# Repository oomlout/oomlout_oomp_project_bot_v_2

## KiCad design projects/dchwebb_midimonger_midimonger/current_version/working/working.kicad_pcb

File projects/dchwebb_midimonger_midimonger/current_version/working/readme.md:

# midimonger
 
## summary 
* id: dchwebb_midimonger_midimonger
* user: dchwebb
* name: midimonger
* board: midimonger
* repo: https://github.com/dchwebb/MidiMonger
* src_file_repo_kicad_pcb: Hardware/MidiMonger.kicad_pcb
* src_file_repo_kicad_pcb_link: https://github.com/dchwebb/MidiMonger/tree/master/Hardware/MidiMonger.kicad_pcb
* src_file_repo_kicad_sch: Hardware/MidiMonger.kicad_sch
* src_file_repo_kicad_sch_link: https://github.com/dchwebb/MidiMonger/tree/master/Hardware/MidiMonger.kicad_sch

* src_file_repo_sch: Hardware/MidiMonger.sch
* src_file_repo_sch_link: https://github.com/dchwebb/MidiMonger/tree/master/Hardware/MidiMonger.sch
* full details link: https://github.com/oomlout/oomlout_oomp_project_bot_v_2/tree/main/projects/dchwebb_midimonger_midimonger/current_version/working

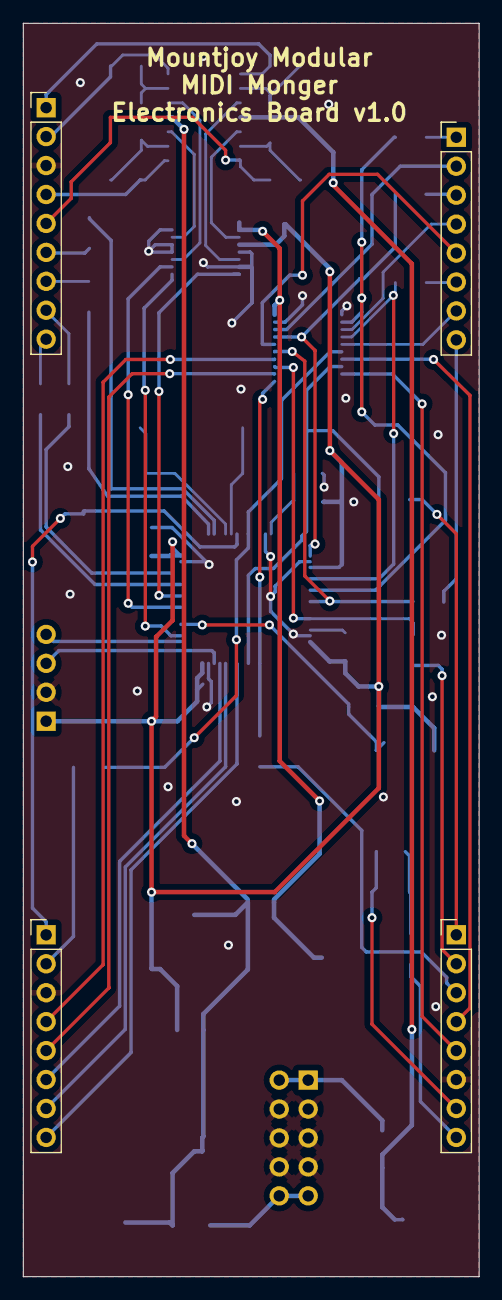
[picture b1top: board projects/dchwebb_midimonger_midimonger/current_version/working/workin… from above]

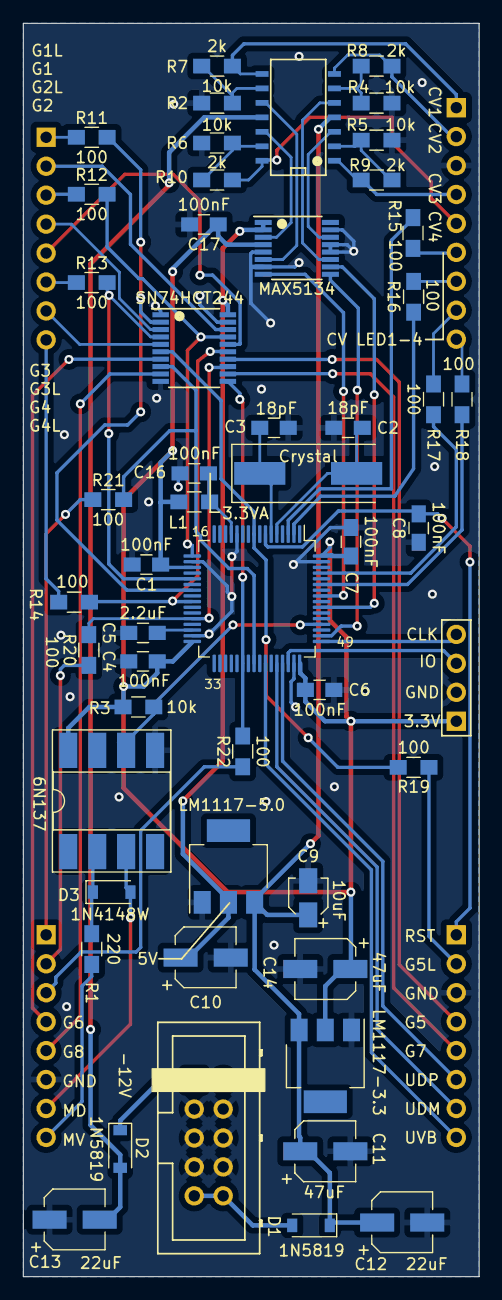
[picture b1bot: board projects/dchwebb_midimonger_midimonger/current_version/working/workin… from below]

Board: 2 copper layers, 40.0 x 110.0 mm, 56 parts (52 on the bottom side), 68 nets.

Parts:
C1, C4, C6, C7, C8, C16, C17: 100nF; C_0805_HandSoldering
C2, C3: 18pF; C_0805_HandSoldering
C5: 2.2uF; C_0805_HandSoldering
C9: 10uF; CP_Elec_3x5.3
C10, C12, C13: 22uF; CP_Elec_5x5.3
C11, C14: 47uF; CP_Elec_5x5.8
D1, D2: 1N5819; D_SOD-123
D3: 1N4148W; D_SOD-123
J1: SWD_Header; SWD_header
J2: Conn_01x09_Male; Socket_Strip_Straight_1x09_Pitch2.54mm
J3, J4, J5: Conn_01x08_Male; Socket_Strip_Straight_1x08_Pitch2.54mm
J9: Eurorack_10_pin_power; Eurorack_10_pin_header
L1: L; L_0805_HandSoldering
R1: 220; R_0805_HandSoldering
R2, R3, R4, R5, R6: 10k; R_0805_HandSoldering
R7, R8, R9, R10: 2k; R_0805_HandSoldering
R11, R12, R13, R14, R15, R16, R17, R18, R19, R20, R21, R22: 100; R_0805_HandSoldering
U1: STM32F446RETx; LQFP-64_10x10mm_P0.5mm
U2: 6N137; DIP-8_W8.89mm_SMDSocket_LongPads
U3: TL074; SOIC-14_N
U4: LM1117-5.0; SOT-223
U5: LM1117-3.3; SOT-223
U6: SN74HCT244; TSSOP-20_4.4x6.5mm_Pitch0.65mm
U7: MAX5134; TSSOP-16_4.4x5mm_Pitch0.65mm
Y1: Crystal; Crystal_SMD

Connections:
+3.3VA: C16.1, L1.1, U1.13
+3V3: C1.1, C4.1, C6.1, C7.1, C14.1, C17.1, J1.1, L1.2, R3.1, U1.19, U1.32, U1.48, U1.64, U2.8, U5.2, U7.4
+5V: C10.1, U4.2, U6.20, U7.1, U7.2
+12V: D1.2, J9.9, J9.10
-12V: D2.1, J9.1, J9.2
CV1_LED: R15.2, U1.3
CV1_LED_OUT: J2.6, R15.1
CV1_OUT: J2.1, R7.1, U3.8
CV2_LED: R16.2, U1.2
CV2_LED_OUT: J2.7, R16.1
CV2_OUT: J2.2, R8.1, U3.7
CV3_LED: R17.2, U1.61
CV3_LED_OUT: J2.8, R17.1
CV3_OUT: J2.4, R9.1, U3.1
CV4_LED: R18.2, U1.59
CV4_LED_OUT: J2.9, R18.1
CV4_OUT: J2.5, R10.1, U3.14
DAC_1: U3.10, U7.6
DAC_2: U3.5, U7.11
DAC_3: U3.3, U7.14
DAC_4: U3.12, U7.3
DAC_MOSI: U1.57, U7.8
DAC_NSS: U1.50, U7.9
DAC_SCK: U1.55, U7.10
GATE1: R11.2, U1.23, U6.2
GATE1_LED_OUT: J3.1, R11.1
GATE1_OUT: J3.2, U6.18
GATE2: R12.2, U1.17, U6.17
GATE2_LED_OUT: J3.3, R12.1
GATE2_OUT: J3.4, U6.3
GATE3: R13.2, U1.21, U6.4
GATE3_LED_OUT: J3.6, R13.1
GATE3_OUT: J3.5, U6.16
GATE4: R14.2, U1.25, U6.15
GATE4_LED_OUT: J3.8, R14.1
GATE4_OUT: J3.7, U6.5
GATE5: R19.2, U1.9, U6.6
GATE5_LED_OUT: J4.2, R19.1
GATE5_OUT: J4.4, U6.14
GATE6: R20.2, U1.28, U6.13
GATE6_LED_OUT: J5.2, R20.1
GATE6_OUT: J5.4, U6.7
GATE7: R21.2, U1.40, U6.8
GATE7_LED_OUT: J5.1, R21.1
GATE7_OUT: J4.5, U6.12
GATE8: R22.2, U1.38, U6.11
GATE8_LED_OUT: J5.3, R22.1
GATE8_OUT: J5.5, U6.9
GND: C1.2, C2.2, C3.2, C4.2, C5.2, C6.2, C7.2, C8.1, C9.2, C10.2, C11.2, C12.2, C13.1, C14.2, C16.2, C17.2, J1.2, J2.3, J4.3, J5.6, J9.3, J9.4, J9.5, J9.6, J9.7, J9.8, R2.1, R4.1, R5.1, R6.1, U1.12, U1.18, U1.31, U1.47, U1.63, U2.5, U4.1, U5.1, U6.1, U6.10, U6.19, U7.5, U7.7, U7.12, U7.13, U7.15
MIDI_DATA: D3.2, J5.7, U2.3
MIDI_RX: R3.2, U1.52, U2.6
MIDI_VREF: J5.8, R1.2
NRST: C8.2, J4.1, U1.7
unnamed: C2.1, U1.5, Y1.2
unnamed: C3.1, U1.6, Y1.1
unnamed: C5.1, U1.30
unnamed: D3.1, R1.1, U2.2
unnamed: R2.2, R7.2, U3.9
unnamed: R4.2, R8.2, U3.6
unnamed: R5.2, R9.2, U3.2
unnamed: R6.2, R10.2, U3.13
SWCLK: J1.4, U1.49
SWDIO: J1.3, U1.46
USB_DM: J4.7, U1.44
USB_DP: J4.6, U1.45
USB_VBUS: J4.8, U1.42
VCC: C9.1, C11.1, C12.1, D1.1, U3.4, U4.3, U5.3
VEE: C13.2, D2.2, U3.11

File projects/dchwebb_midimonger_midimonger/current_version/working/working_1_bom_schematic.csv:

"Source:","C:\gh\oomlout_oomp_project_bot_v_2\projects\dchwebb_midimonger_midimonger\current_version\working\working_1.kicad_sch"
"Date:","30/09/2023 04:30:42"
"Tool:","Eeschema 7.0.6"
"Generator:","C:/Program Files/KiCad/7.0/bin/scripting/plugins/bom_csv_grouped_by_value_with_fp.py"
"Component Count:","56"
"Ref","Qnty","Value","Cmp name","Footprint","Description","Vendor","DNP"
"C1, C4, C6, C7, C8, C16, C17","7","100nF","C","Capacitors_SMD:C_0805_HandSoldering","Unpolarized capacitor","",""
"C2, C3","2","18pF","C","Capacitors_SMD:C_0805_HandSoldering","Unpolarized capacitor","",""
"C5","1","2.2uF","C","Capacitors_SMD:C_0805_HandSoldering","Unpolarized capacitor","",""
"C9","1","10uF","C","Capacitors_SMD:CP_Elec_3x5.3","Unpolarized capacitor","",""
"C10, C12, C13","3","22uF","CP-Device","Capacitors_SMD:CP_Elec_5x5.3","","",""
"C11, C14","2","47uF","C","Capacitors_SMD:CP_Elec_5x5.8","Unpolarized capacitor","",""
"D1, D2","2","1N5819","1N5819","Diodes_SMD:D_SOD-123","40V 1A Schottky Barrier Rectifier Diode, DO-41","",""
"D3","1","1N4148W","1N4148W","Diodes_SMD:D_SOD-123","75V 0.15A Fast Switching Diode, SOD-123","",""
"J1","1","SWD_Header","Conn_01x04_Male","Custom_Footprints:SWD_header","Generic connector, single row, 01x04, script generated (kicad-library-utils/schlib/autogen/connector/)","",""
"J2","1","Conn_01x09_Male","Conn_01x09_Male","Socket_Strips:Socket_Strip_Straight_1x09_Pitch2.54mm","Generic connector, single row, 01x09, script generated (kicad-library-utils/schlib/autogen/connector/)","",""
"J3, J4, J5","3","Conn_01x08_Male","Conn_01x08_Male","Socket_Strips:Socket_Strip_Straight_1x08_Pitch2.54mm","Generic connector, single row, 01x08, script generated (kicad-library-utils/schlib/autogen/connector/)","",""
"J9","1","Eurorack_10_pin_power","Eurorack_10_pin_power","Custom_Footprints:Eurorack_10_pin_header","","",""
"L1","1","L","L","Inductors_SMD:L_0805_HandSoldering","Inductor","",""
"R1","1","220","R","Resistors_SMD:R_0805_HandSoldering","Resistor","",""
"R2, R3, R4, R5, R6","5","10k","R","Resistors_SMD:R_0805_HandSoldering","Resistor","",""
"R7, R8, R9, R10","4","2k","R","Resistors_SMD:R_0805_HandSoldering","Resistor","",""
"R11, R12, R13, R14, R15, R16, R17, R18, R19, R20, R21, R22","12","100","R","Resistors_SMD:R_0805_HandSoldering","Resistor","",""
"U1","1","STM32F446RETx","STM32F446RETx","Package_QFP:LQFP-64_10x10mm_P0.5mm","ARM Cortex-M4 MCU, 512KB flash, 128KB RAM, 180MHz, 1.8-3.6V, 50 GPIO, LQFP-64","",""
"U2","1","6N137","6N137","Housings_DIP:DIP-8_W8.89mm_SMDSocket_LongPads","High Speed Optocoupler, TTL Compatible, CTR 18%, DIP8","",""
"U3","1","TL074","TL074","SMD_Packages:SOIC-14_N","Quad Low-Noise JFET-Input Operational Amplifiers, DIP-14/SOIC-14","",""
"U4","1","LM1117-5.0","LM1117-5.0","TO_SOT_Packages_SMD:SOT-223","800mA Low-Dropout Linear Regulator, 5.0V fixed output, TO-220/TO-252/TO-263/SOT-223","",""
"U5","1","LM1117-3.3","LM1117-3.3","TO_SOT_Packages_SMD:SOT-223","800mA Low-Dropout Linear Regulator, 3.3V fixed output, TO-220/TO-252/TO-263/SOT-223","",""
"U6","1","SN74HCT244","SN74HCT244","Housings_SSOP:TSSOP-20_4.4x6.5mm_Pitch0.65mm","Octal-Channel Buffer & Line Driver, 3-State, 20-Pin TSSOP","",""
"U7","1","MAX5134","MAX5134","Housings_SSOP:TSSOP-16_4.4x5mm_Pitch0.65mm","Maxim MAX5134AGUE+, 4-Channel Serial DAC, 16-Pin TSSOP","",""
"Y1","1","Crystal","Crystal","Custom_Footprints:Crystal_SMD","Two pin crystal","",""

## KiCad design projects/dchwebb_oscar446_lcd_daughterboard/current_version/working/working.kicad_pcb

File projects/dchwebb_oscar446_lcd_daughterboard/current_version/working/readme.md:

# oscar446
 
## summary 
* id: dchwebb_oscar446_lcd_daughterboard
* user: dchwebb
* name: oscar446
* board: lcd_daughterboard
* repo: https://github.com/dchwebb/Oscar446
* src_file_repo_kicad_pcb: Hardware/lcd_Daughterboard.kicad_pcb
* src_file_repo_kicad_pcb_link: https://github.com/dchwebb/Oscar446/tree/master/Hardware/lcd_Daughterboard.kicad_pcb

* src_file_repo_sch: Hardware/lcd_Daughterboard.sch
* src_file_repo_sch_link: https://github.com/dchwebb/Oscar446/tree/master/Hardware/lcd_Daughterboard.sch
* full details link: https://github.com/oomlout/oomlout_oomp_project_bot_v_2/tree/main/projects/dchwebb_oscar446_lcd_daughterboard/current_version/working

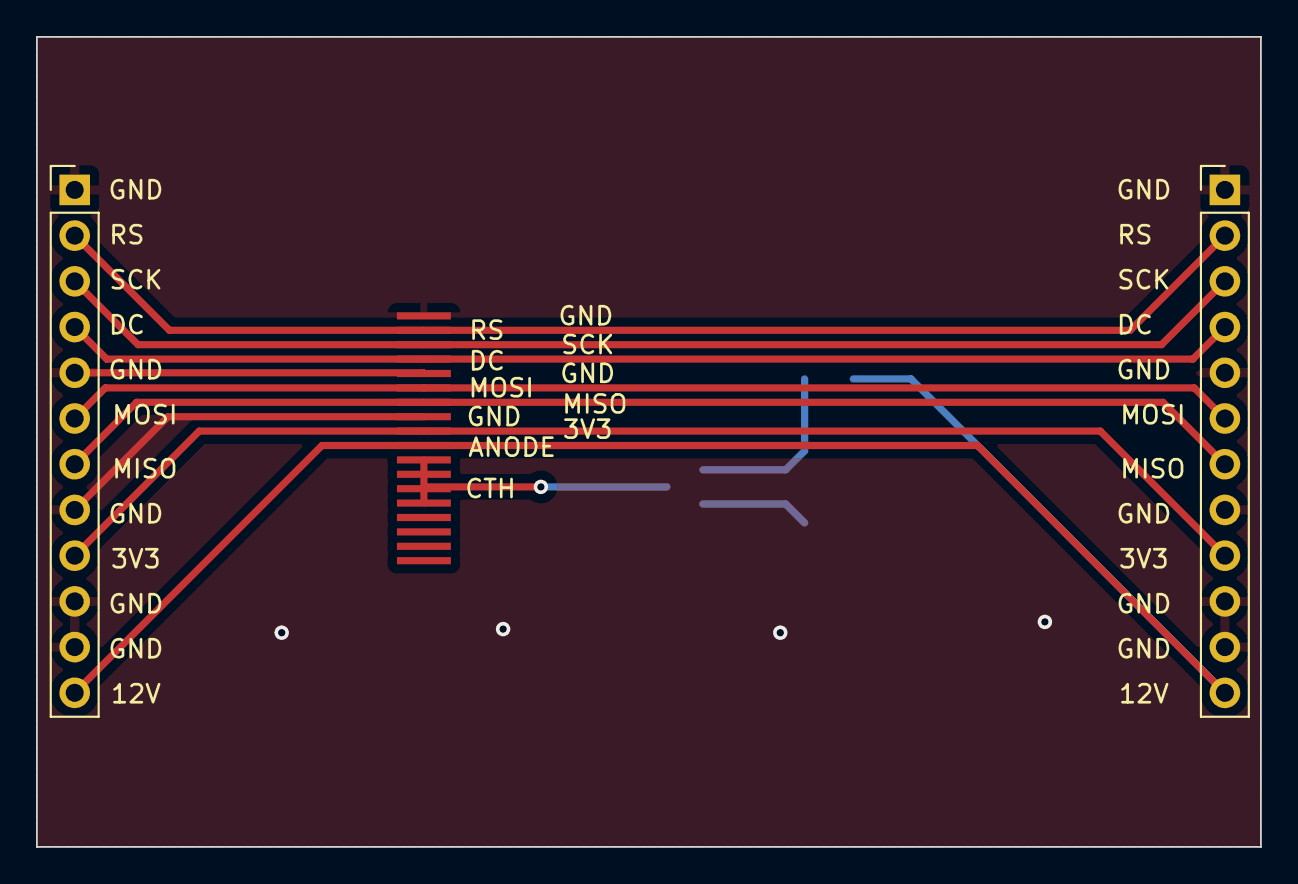
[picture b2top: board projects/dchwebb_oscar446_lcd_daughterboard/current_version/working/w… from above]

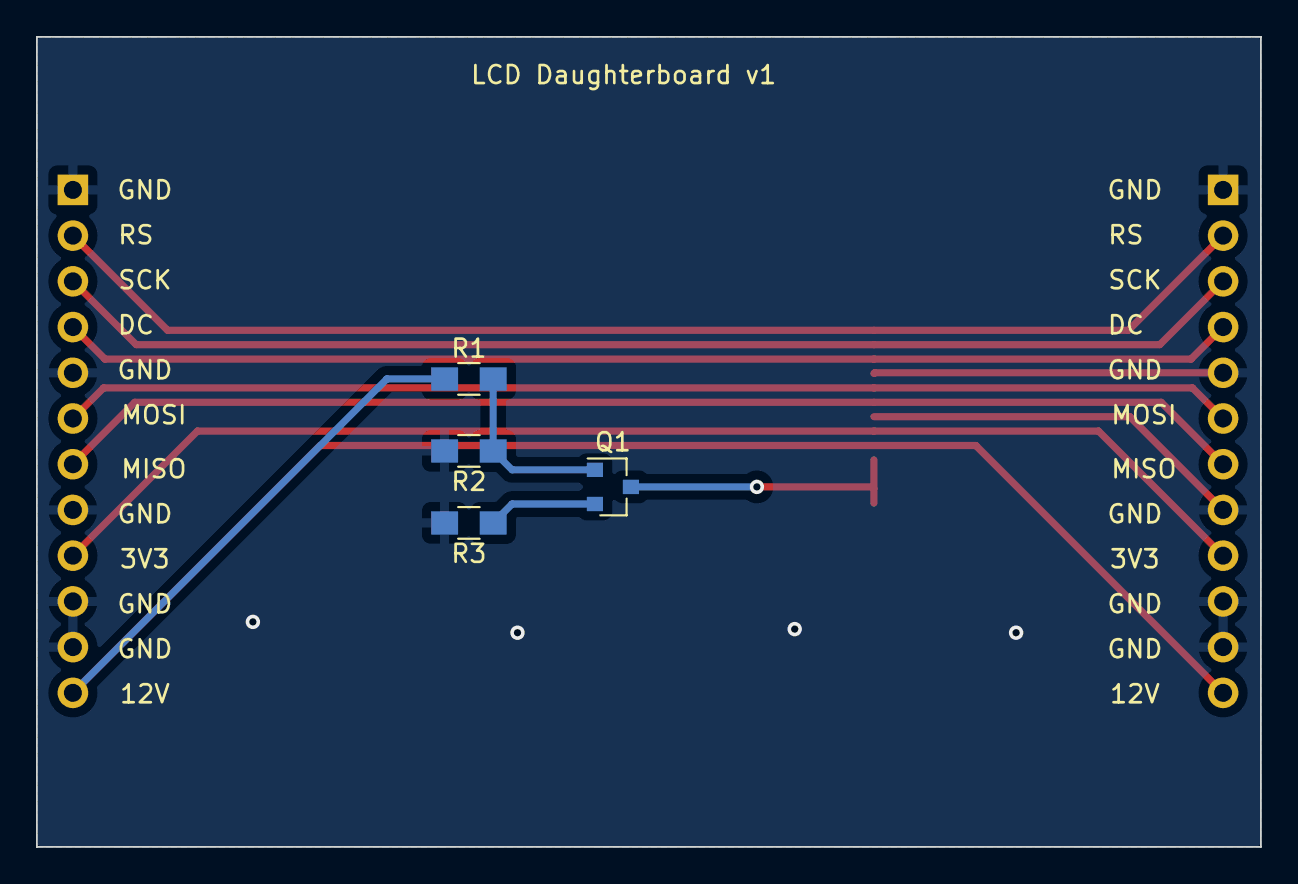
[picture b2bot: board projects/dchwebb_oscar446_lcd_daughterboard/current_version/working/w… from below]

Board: 2 copper layers, 68.0 x 45.0 mm, 7 parts (4 on the bottom side), 11 nets.

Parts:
J1, J2: Conn_01x12; Pin_Header_Straight_1x12_Pitch2.54mm
Q1: MMBT3904; SOT-23
R1: 220; R_0805_HandSoldering
R2: 1k; R_0805_HandSoldering
R3: 100; R_0805_HandSoldering
U1: ILI9341_SPI_Bare; 18x0.8mmLCDConnector

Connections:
+3V3: J1.9, J2.9, U1.9
GND: J1.1, J1.5, J1.8, J1.10, J1.11, J2.1, J2.5, J2.8, J2.10, J2.11, R2.2, R3.2, U1.1, U1.5, U1.8
LCD_CATHODE: Q1.3, U1.11, U1.12, U1.13, U1.14
LCD_DC: J1.4, J2.4, U1.4
LCD_MISO: J1.7, J2.7, U1.7
LCD_MOSI: J1.6, J2.6, U1.6
LCD_RESET: J1.2, J2.2, U1.2
LCD_SCK: J1.3, J2.3, U1.3
unnamed: Q1.1, R1.2, R2.1
unnamed: Q1.2, R3.1
VCC: J1.12, J2.12, R1.1, U1.10

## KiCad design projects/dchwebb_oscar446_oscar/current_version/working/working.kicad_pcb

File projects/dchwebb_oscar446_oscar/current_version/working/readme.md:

# oscar446
 
## summary 
* id: dchwebb_oscar446_oscar
* user: dchwebb
* name: oscar446
* board: oscar
* repo: https://github.com/dchwebb/Oscar446
* src_file_repo_kicad_pcb: Hardware/v1_bu/oscar.kicad_pcb
* src_file_repo_kicad_pcb_link: https://github.com/dchwebb/Oscar446/tree/master/Hardware/v1_bu/oscar.kicad_pcb

* src_file_repo_sch: Hardware/v1_bu/oscar.sch
* src_file_repo_sch_link: https://github.com/dchwebb/Oscar446/tree/master/Hardware/v1_bu/oscar.sch
* full details link: https://github.com/oomlout/oomlout_oomp_project_bot_v_2/tree/main/projects/dchwebb_oscar446_oscar/current_version/working

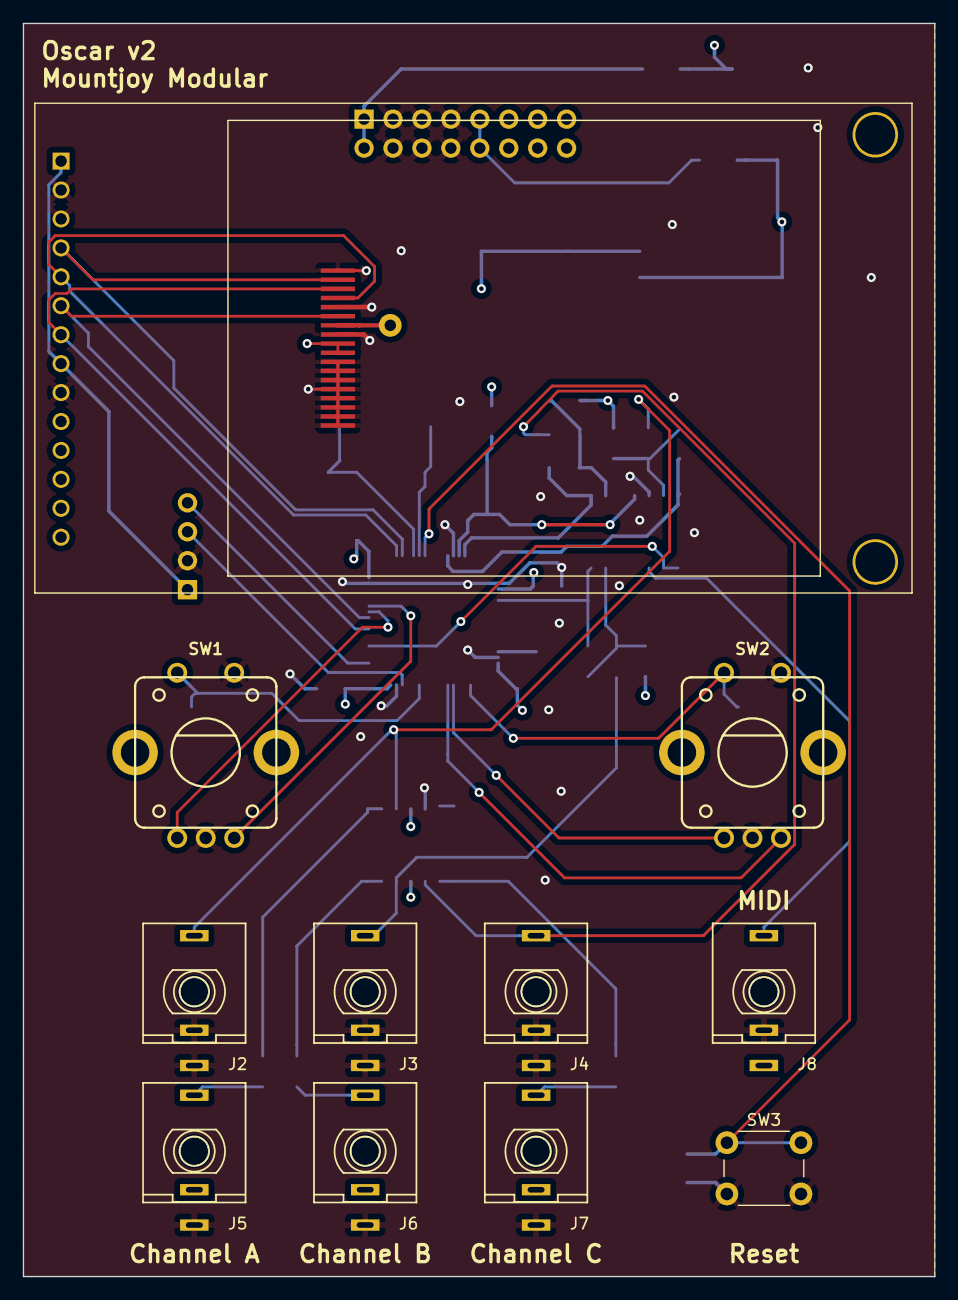
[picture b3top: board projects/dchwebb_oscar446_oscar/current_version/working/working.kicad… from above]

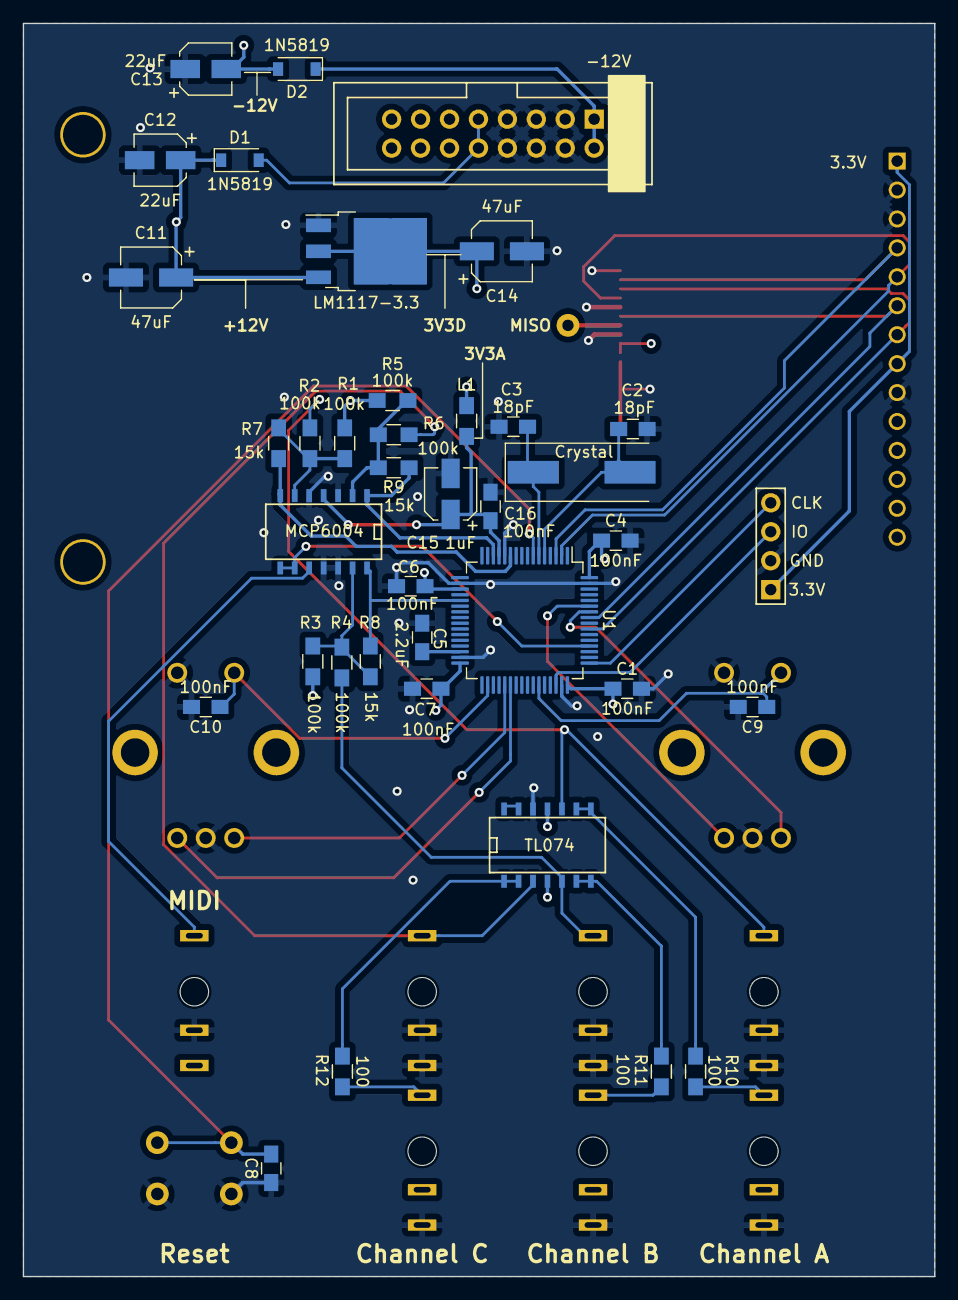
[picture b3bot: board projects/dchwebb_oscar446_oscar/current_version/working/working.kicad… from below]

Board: 4 copper layers, 80.0 x 110.0 mm, 51 parts (38 on the bottom side), 42 nets.

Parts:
C1, C4, C6, C7, C8, C9, C10, C16: 100nF; C_0805_HandSoldering
C2, C3: 18pF; C_0805_HandSoldering
C5: 2.2uF; C_0805_HandSoldering
C11, C14: 47uF; CP_Elec_5x5.8
C12, C13: 22uF; CP_Elec_4x5.8
C15: 1uF; CP_Elec_4x5.8
D1, D2: 1N5819; D_SOD-123
J1: SWD_Header; SWD_header
J2: ChannelA_In; THONKICONN_hole
J3: ChannelB_In; THONKICONN_hole
J4: ChannelC_In; THONKICONN_hole
J5: ChA_Buff_Out; THONKICONN_hole
J6: ChB_Buff_Out; THONKICONN_hole
J7: ChC_Buff_Out; THONKICONN_hole
J8: MIDI_In; THONKICONN_hole
J9: Eurorack_16_pin_power; Eurorack_16_pin_header
J10: LCD_Connector; 18x0.8mmLCDConnector
J11: MISO_Connector; SolderWirePad_single_2mmDrill
L1: L; R_0805_HandSoldering
R1, R2, R3, R4, R5, R6: 100k; R_0805_HandSoldering
R7, R8, R9: 15k; R_0805_HandSoldering
R10, R11, R12: 100; R_0805_HandSoldering
SW1: Left_Encoder; Encoder
SW2: Right_Encoder; Encoder
SW3: SW_Push; SW_PUSH_6mm
U1: STM32F446RETx; LQFP-64_10x10mm_P0.5mm
U2: ILI9341_SPI
U3: MCP6004; SOIC-14_N
U4: TL074; SOIC-14_N
U5: LM1117-3.3; TO-252-3_TabPin2
Y1: Crystal; Crystal_SMD

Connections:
+3.3VA: C15.1, C16.1, L1.1, U1.13, U3.4
+3V3: C1.1, C4.1, C6.1, C7.1, C14.1, J1.1, J10.9, J10.10, L1.2, U1.19, U1.32, U1.48, U1.64, U2.1, U2.8, U5.2
+12V: D1.2, J9.9, J9.10
-12V: D2.1, J9.1, J9.2
/CHA_In: J2.3, R2.2, U4.10
/CHA_Out: J5.3, R10.1
/CHB_In: J3.3, R4.2, U4.5
/CHB_Out: J6.3, R11.1
/CHC_In: J4.3, R6.2, U4.3
/CHC_Out: J7.3, R12.1
/MIDI_In: J8.3, U3.10
CH_A_IN: R7.1, U1.11, U3.7
CH_B_IN: R8.1, U1.21, U3.14
CH_C_IN: R9.1, U1.14, U3.1
GND: C1.2, C2.2, C3.2, C4.2, C5.2, C6.2, C7.2, C8.1, C9.2, C10.2, C11.2, C12.2, C13.1, C14.2, C15.2, C16.2, J1.2, J2.1, J2.2, J3.1, J3.2, J4.1, J4.2, J5.1, J6.1, J7.1, J8.2, J9.3, J9.4, J9.5, J9.6, J9.7, J9.8, J10.1, J10.5, J10.8, J10.11, J10.12, J10.13, J10.14, J10.15, J10.16, J10.17, J10.18, SW1.C, SW1.S2, SW2.C, SW2.S2, SW3.2, U1.12, U1.18, U1.31, U1.47, U1.63, U2.2, U2.3, U2.9, U3.3, U3.5, U3.11, U3.12, U4.12, U5.1
LCD_DC: J10.4, U1.2, U2.5
LCD_MISO: J10.7, J11.1
LCD_MOSI: J10.6, U1.57, U2.6
LCD_RESET: J10.2, U1.3, U2.4
LCD_SCK: J10.3, U1.55, U2.7
L_ENC_BTN: C9.1, SW1.S1, U1.43
L_ENC_DN: SW1.B, U1.59
L_ENC_UP: SW1.A, U1.58
MIDI_OUT: U1.52, U3.8, U3.9
NRST: C8.2, SW3.1, U1.7
unnamed: C2.1, U1.5, Y1.2
unnamed: C3.1, U1.6, Y1.1
unnamed: C5.1, U1.30
unnamed: R1.1, R2.1, R7.2, U3.6
unnamed: R3.1, R4.1, R8.2, U3.13
unnamed: R5.1, R6.1, R9.2, U3.2
unnamed: R10.2, U4.8, U4.9
unnamed: R11.2, U4.6, U4.7
unnamed: R12.2, U4.1, U4.2
unnamed: U4.13, U4.14
R_ENC_BTN: C10.1, SW2.S1, U1.34
R_ENC_DN: SW2.B, U1.38
R_ENC_UP: SW2.A, U1.37
SWCLK: J1.4, U1.49
SWDIO: J1.3, U1.46
VCC: C11.1, C12.1, D1.1, U4.4, U5.3
VEE: C13.2, D2.2, R1.2, R3.2, R5.2, U4.11
